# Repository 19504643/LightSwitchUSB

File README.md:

# SushiBits LightSwitch-USB

This is a simple-ish USB-controlled LED light switch, intended to be used along
with IKEA USB powered LED lights.

For me this gadget is intended to play nice with my KVM tree, which would share
the LED Lamp (along with other peripherals) across computers. This is one of the
reason why a custom USB device is needed, since being a full USB device would
allow the computer, and the software running on it, to tell if the LED is online
or not. It also tells whether the computer is active on KVM or not.

## Comapnion Software:

* Firmware: https://github.com/SushiBits/LightSwitchUSB-Firmware
* Host software for macOS: https://github.com/SushiBits/LightSwitchUSB-Mac
* Host software for Windows
* Host software for Linux

## License and Contact

This project is licensed under the [3-clause BSD license](LICENSE.md).

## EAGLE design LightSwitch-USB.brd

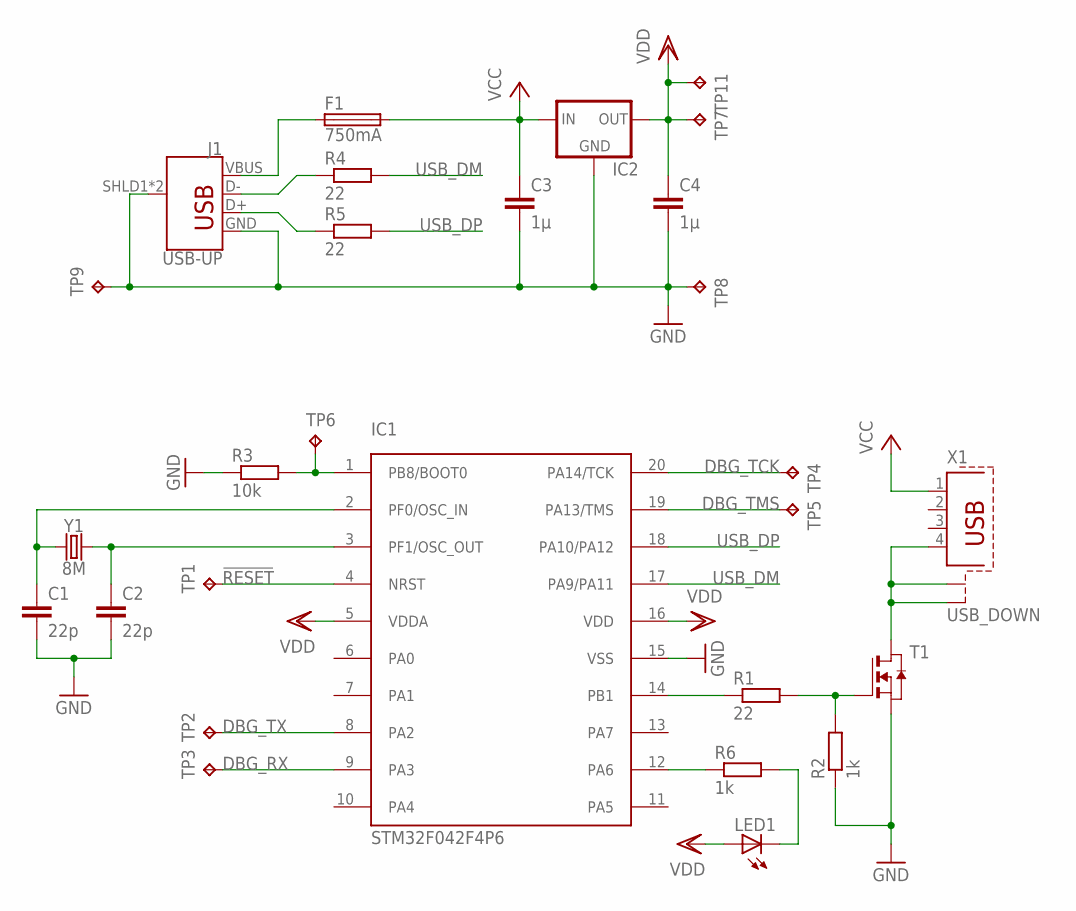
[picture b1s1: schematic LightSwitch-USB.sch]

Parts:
C1, C2: 22p; C0603
C3, C4: 1µ; C0603
F1: 750mA; R1206
IC1: STM32F042F4P6; TSSOP20
IC2: XC63FPM; SOT23
J1: USB-UP; USB-A-H
LED1: LEDCHIP-LED0805; CHIP-LED0805
R1, R4, R5: 22; R0603
R2, R6: 1k; R0603
R3: 10k; R0603
T1: NMOSSOT23; SOT-23
TP1, TP2, TP3, TP4, TP5, TP6, TP7, TP8, TP9, TP11: TPB1,27; B1,27
X1: USB_DOWN; PN87520-S
Y1: 8M; CRYSTAL-SMD-5X3.2-2PAD

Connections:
!RESET: IC1.4 (NRST), TP1.TP
DBG_RX: IC1.9 (PA3), TP3.TP
DBG_TCK: IC1.20 (PA14/TCK), TP4.TP
DBG_TMS: IC1.19 (PA13/TMS), TP5.TP
DBG_TX: IC1.8 (PA2), TP2.TP
GND: C1.2, C2.2, C3.2, C4.2, IC1.15 (VSS), IC2.1 (GND), J1.GND, J1.SHLD1 (SHIELD), J1.SHLD2 (SHIELD), R2.1, R3.1, T1.2 (S), TP8.TP, TP9.TP
unnamed: T1.1 (D), X1.4, X1.S1, X1.S2
unnamed: LED1.C, R6.2
unnamed: IC1.12 (PA6), R6.1
OUT_DRV: IC1.14 (PB1), R1.1
OUT_GATE: R1.2, R2.2, T1.3 (G)
SYS_BOOT: IC1.1 (PB8/BOOT0), R3.2, TP6.TP
SYS_XIN: C1.1, IC1.2 (PF0/OSC_IN), Y1.P$1 (1)
SYS_XOUT: C2.1, IC1.3 (PF1/OSC_OUT), Y1.P$2 (2)
USB+: J1.D+, R5.1
USB-: J1.D-, R4.1
USB_DM: IC1.17 (PA9/PA11), R4.2
USB_DP: IC1.18 (PA10/PA12), R5.2
VBUS: F1.1, J1.VBUS
VCC: C3.1, F1.2, IC2.3 (IN), X1.1
VDD: C4.1, IC1.5 (VDDA), IC1.16 (VDD), IC2.2 (OUT), LED1.A, TP7.TP, TP11.TP

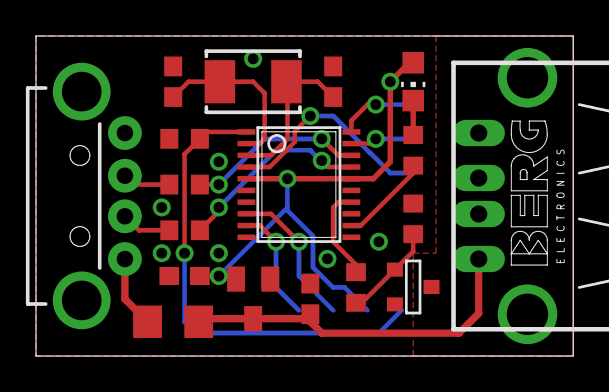
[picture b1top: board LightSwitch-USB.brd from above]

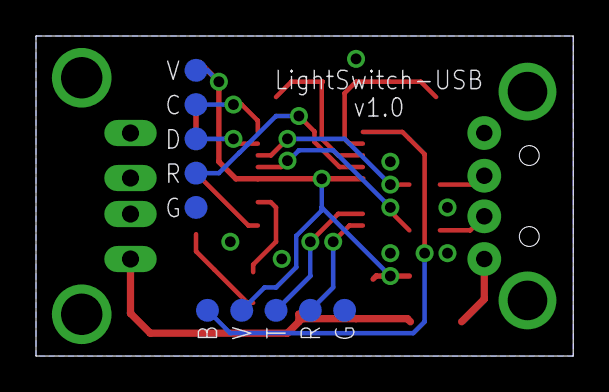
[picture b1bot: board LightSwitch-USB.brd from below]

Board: 2 copper layers, 29.8 x 17.8 mm, 28 parts (10 on the bottom side), 21 nets.

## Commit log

2017-10-17 The LightSwitchUSB files
2017-10-17 Added a README and LICENSE
2017-10-22 Added mentions to companion software.

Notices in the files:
parts and their libraries:
SparkFun-Connectors: Licensing: Creative Commons ShareAlike 4.0 International - https://creativecommons.org/licenses/by-sa/4.0
